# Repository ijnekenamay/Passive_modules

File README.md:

# Passive_modules
This is a passive outboard device for modular synths and can be used a "bare"PCB.
It can be produced by submitting the Gerber file for PCB to a production company in China.
- - Some of the products are Eurorack-standard.

## DiodeORLogic

- This is a simple circuit mainly for mixing GATE/TRIGGER.
- It is 8in and 1out.
- P&P file and BOM are included so that you can use SMT assembly with JLCPCB etc.
- I use a 3.5mm stereo jack called PJ311. Unnecessary pins for stereo are floated. If you need a large quantity, you can purchase it from [Aliexpress under the part number PJ342.](https://ja.aliexpress.com/item/4000661854237.html)
- It has actually been manufactured and is working well. 

## Passive multiple

- It was not actually manufactured. There is no guarantee of operation at this time.
- I use a 3.5mm stereo jack called PJ311. Unnecessary pins for stereo are floated. If you need a large quantity, you can purchase it from [Aliexpress under the part number PJ342.](https://ja.aliexpress.com/item/4000661854237.html)

## 2hp switched multiple
- This is actually inspired by the Switched Multiple in "Extralife".[MUST BE WATCH](https://youtu.be/l3i5O9jBNbY)
- This is data for Eurorack format panels only; when submitting to PCB Fab, it is recommended that they be manufactured in aluminum sheet.
- EASY!

## micro passive multiple
- This is an alternative to stackable cables. It is a PCB with only 3 TIPs and GND connected.
- It was not actually manufactured. There is no guarantee of operation at this time.
- I use a 3.5mm stereo jack called PJ311. Unnecessary pins for stereo are floated. If you need a large quantity, you can purchase it from [Aliexpress under the part number PJ342.](https://ja.aliexpress.com/item/4000661854237.html)

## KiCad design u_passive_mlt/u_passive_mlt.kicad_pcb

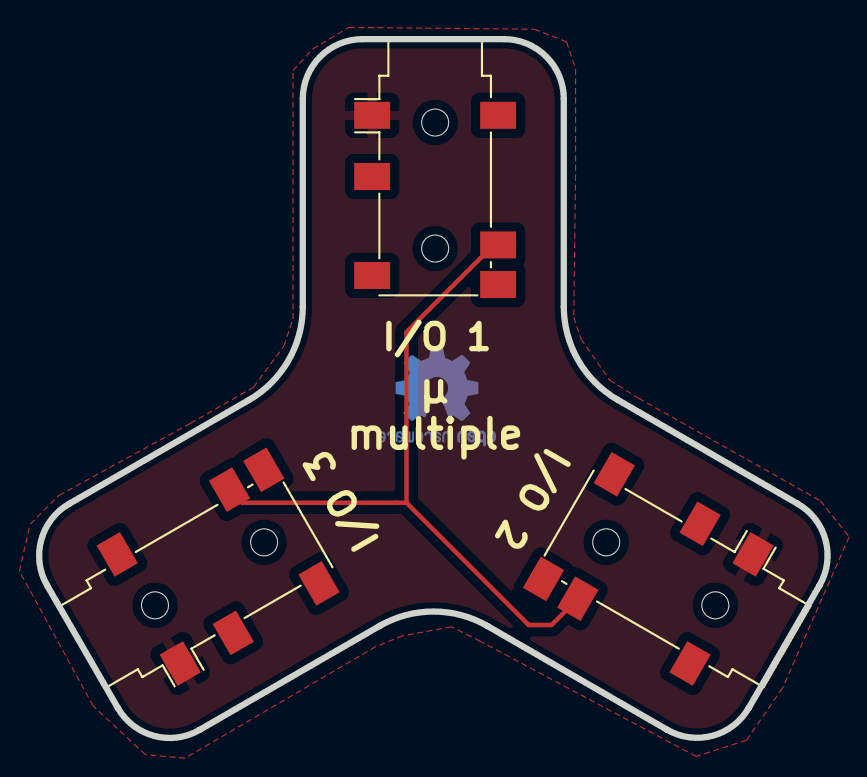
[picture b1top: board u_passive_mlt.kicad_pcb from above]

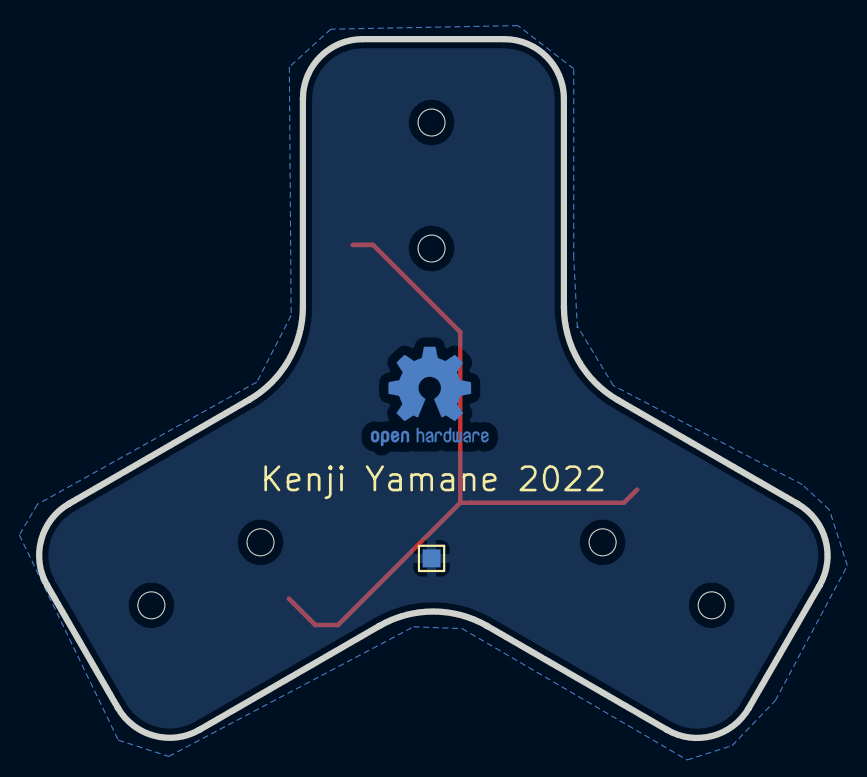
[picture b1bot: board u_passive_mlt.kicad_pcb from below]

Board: 2 copper layers, 43.8 x 38.8 mm, 5 parts (2 on the bottom side), 2 nets.

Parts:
J1: 1; Jack_3.5mm_PJ311_Horizontal
J2: 2; Jack_3.5mm_PJ311_Horizontal
J3: 3; Jack_3.5mm_PJ311_Horizontal
REF1: 1mm; TestPoint_Pad_1.0x1.0mm
REF2: OSHW-Logo2_7.3x6mm_Copper

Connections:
GND: J1.1, J2.1, J3.1
T: J1.4, J2.4, J3.4

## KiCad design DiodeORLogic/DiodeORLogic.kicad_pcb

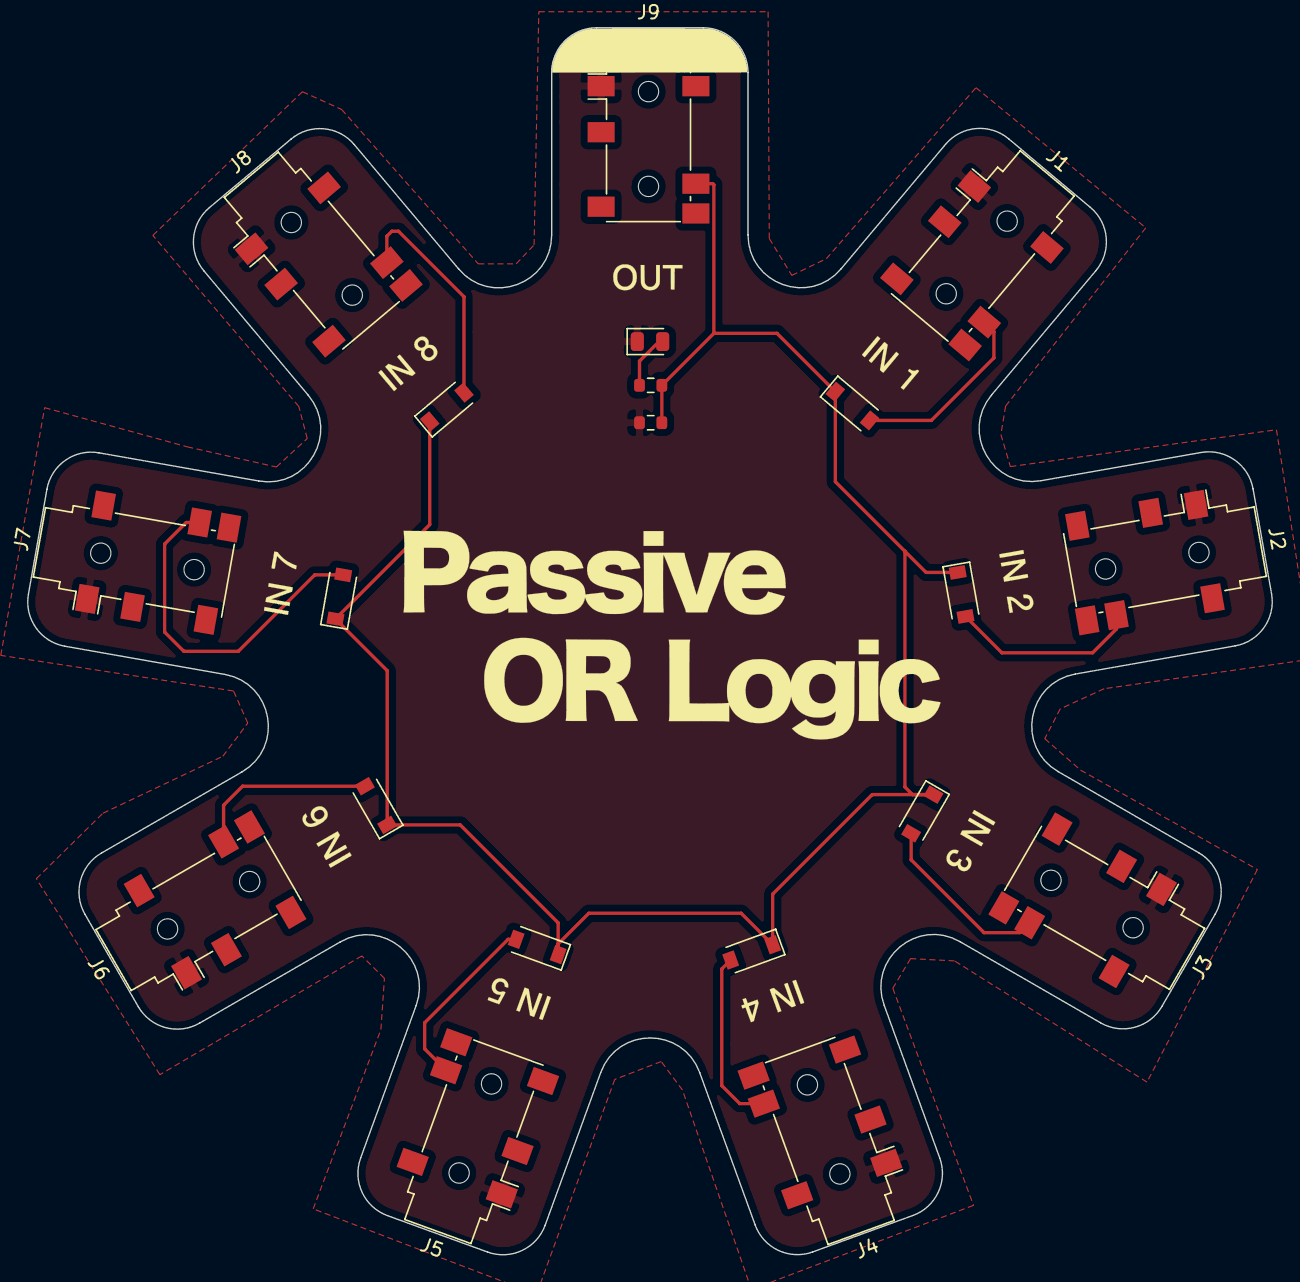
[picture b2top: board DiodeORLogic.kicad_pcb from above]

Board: 2 copper layers, 91.9 x 90.6 mm, 21 parts (1 on the bottom side), 11 nets.

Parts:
D1, D2, D3, D4, D5, D6, D7, D8: 1N4148; D_SOD-123
D10: LED; LED_0805_2012Metric
J1: INPUT1; Jack_3.5mm_PJ311_Horizontal
J2: INPUT2; Jack_3.5mm_PJ311_Horizontal
J3: INPUT3; Jack_3.5mm_PJ311_Horizontal
J4: INPUT4; Jack_3.5mm_PJ311_Horizontal
J5: INPUT5; Jack_3.5mm_PJ311_Horizontal
J6: INPUT6; Jack_3.5mm_PJ311_Horizontal
J7: INPUT7; Jack_3.5mm_PJ311_Horizontal
J8: INPUT8; Jack_3.5mm_PJ311_Horizontal
J9: OUT; Jack_3.5mm_PJ311_Horizontal
R1: 10k; R_0603_1608Metric
R2: 1k; R_0603_1608Metric
REF1: TestPoint_Pad_1.0x1.0mm

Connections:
GND: D10.1, J1.1, J2.1, J3.1, J4.1, J5.1, J6.1, J7.1, J8.1, J9.1, R1.1, REF1.1
unnamed: D1.1, D2.1, D3.1, D4.1, D5.1, D6.1, D7.1, D8.1, J9.4, R1.2, R2.2
unnamed: D1.2, J1.4
unnamed: D2.2, J2.4
unnamed: D3.2, J3.4
unnamed: D4.2, J4.4
unnamed: D5.2, J5.4
unnamed: D6.2, J6.4
unnamed: D7.2, J7.4
unnamed: D8.2, J8.4
unnamed: D10.2, R2.1

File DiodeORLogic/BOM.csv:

Comment,Designator, Footprint
1N4148,D1,Diode_SMD:D_SOD-123
1N4148,D2,Diode_SMD:D_SOD-123
1N4148,D3,Diode_SMD:D_SOD-123
1N4148,D4,Diode_SMD:D_SOD-123
1N4148,D5,Diode_SMD:D_SOD-123
1N4148,D6,Diode_SMD:D_SOD-123
1N4148,D7,Diode_SMD:D_SOD-123
1N4148,D8,Diode_SMD:D_SOD-123
10k,R1,Resistor_SMD:R_0603_1608Metric
1k,R2,Resistor_SMD:R_0603_1608Metric
LED,D10,LED_SMD:LED_0805_2012Metric

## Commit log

2022-02-25 AddFile
2022-06-15 Add new stuff
